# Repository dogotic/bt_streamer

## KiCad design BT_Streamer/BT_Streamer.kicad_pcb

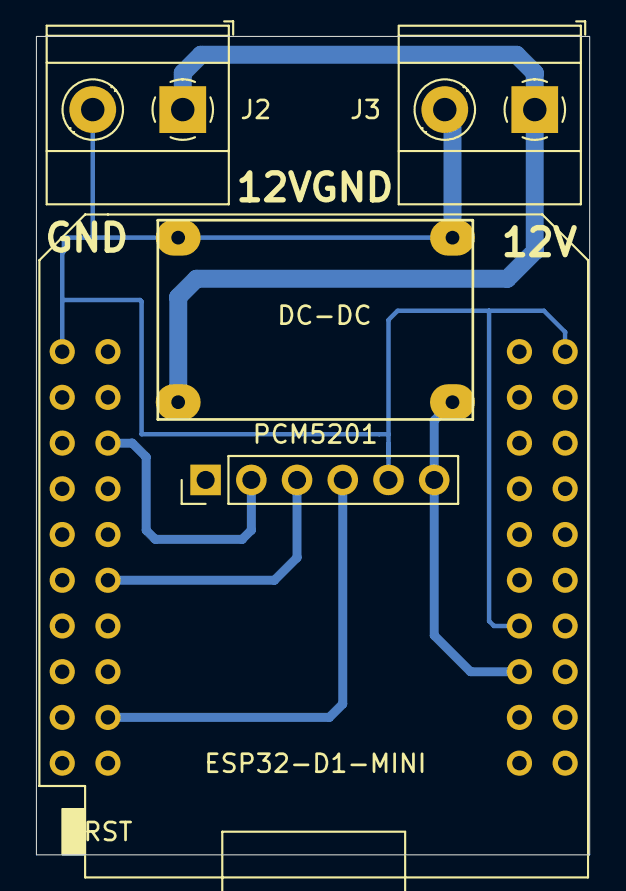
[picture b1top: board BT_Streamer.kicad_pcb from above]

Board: 2 copper layers, 30.7 x 45.5 mm, 5 parts (0 on the bottom side), 6 nets.

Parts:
DC-DC: Mini360; Mini360_step-down
ESP32-D1-MINI: mini_esp32; ESP32_mini
J2: +12V_IN; TerminalBlock_Phoenix_MKDS-1,5-2_1x02_P5.00mm_Horizontal
J3: +12V_OUT; TerminalBlock_Phoenix_MKDS-1,5-2_1x02_P5.00mm_Horizontal
PCM5201: PCM5102; PinHeader_1x06_P2.54mm_Vertical

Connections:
+5V: DC-DC.4, ESP32-D1-MINI.35, PCM5201.6
+12V: DC-DC.2, J2.1, J3.1
BCK: ESP32-D1-MINI.6, PCM5201.2
DIN: ESP32-D1-MINI.12, PCM5201.3
GND: DC-DC.1, DC-DC.3, ESP32-D1-MINI.1, ESP32-D1-MINI.22, ESP32-D1-MINI.33, J2.2, J3.2, PCM5201.5
LCK: ESP32-D1-MINI.18, PCM5201.4

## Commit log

2024-05-18 prvi commit
2024-12-30 nesto?!
